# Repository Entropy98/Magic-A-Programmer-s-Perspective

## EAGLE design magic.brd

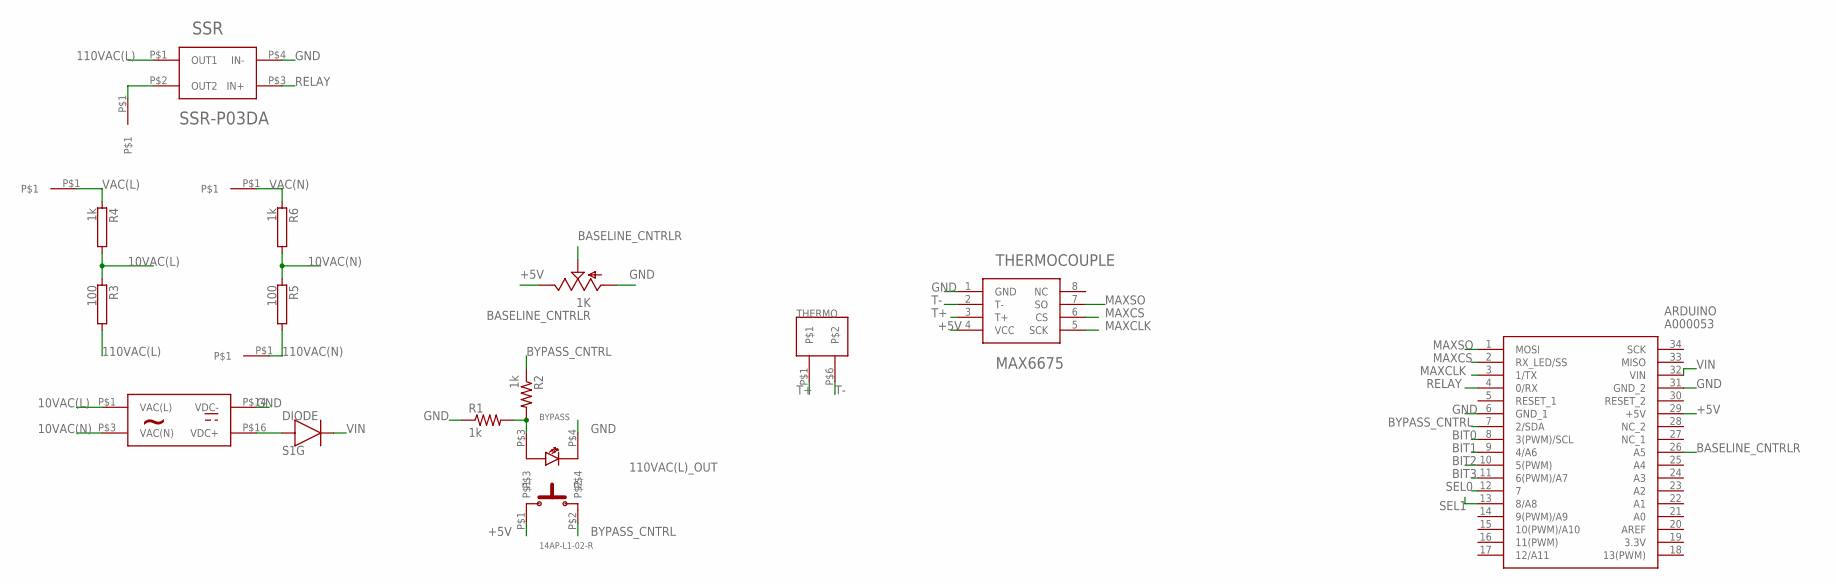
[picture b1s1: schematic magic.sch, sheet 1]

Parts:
110VAC(L)_OUT, 110VAC(N)_OUT: 6-GAUGE
AC(L)_IN: 6-GAUGE
AC(N)_IN: 6-GAUGE
ARDUINO: A000053; HDRV34W70P1570X254_2X17_4900X1
BASELINE_CNTRLR: 1K; PT-10
BYPASS: 14AP-L1-02-R; 14XX-LX-0X-X
DIODE: S1G
R1, R2: 1k; M1206
R3, R5: 100; TO-247-2V
R4, R6: 1k; TO-247-2V
SSR: SSR-P03DA
THERMO: PC6-16/2-G1-10,16
THERMOCOUPLE: MAX6675
TRANSFORMER: RAC04-09SC

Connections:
10VAC(L): R3.1, R4.2, TRANSFORMER.P$1 (VAC(L))
10VAC(N): R5.1, R6.2, TRANSFORMER.P$3 (VAC(N))
110VAC(L): R3.2, SSR.P$1 (OUT1)
110VAC(L)_OUT: 110VAC(L)_OUT.P$1, SSR.P$2 (OUT2)
110VAC(N): 110VAC(N)_OUT.P$1, R5.2
+5V: ARDUINO.29 (+5V), BASELINE_CNTRLR.E, BYPASS.P$1, THERMOCOUPLE.4 (VCC); also elsewhere on the board
BASELINE_CNTRLR: ARDUINO.26 (A5), BASELINE_CNTRLR.S
BIT0: ARDUINO.8 (3(PWM)/SCL); also elsewhere on the board
BIT1: ARDUINO.9 (4/A6); also elsewhere on the board
BIT2: ARDUINO.10 (5(PWM)); also elsewhere on the board
BIT3: ARDUINO.11 (6(PWM)/A7); also elsewhere on the board
BYPASS_CNTRL: ARDUINO.7 (2/SDA), BYPASS.P$2, R2.1
GND: ARDUINO.6 (GND_1), ARDUINO.31 (GND_2), BASELINE_CNTRLR.A, BYPASS.P$4, R1.1, SSR.P$4 (IN-), THERMOCOUPLE.1 (GND), TRANSFORMER.P$14 (VDC-); also elsewhere on the board
MAXCLK: ARDUINO.3 (1/TX), THERMOCOUPLE.5 (SCK)
MAXCS: ARDUINO.2 (RX_LED/SS), THERMOCOUPLE.6 (CS)
MAXSO: ARDUINO.1 (MOSI), THERMOCOUPLE.7 (SO)
unnamed: DIODE.2, TRANSFORMER.P$16 (VDC+)
unnamed: BYPASS.P$3, R1.2, R2.2
RELAY: ARDUINO.4 (0/RX), SSR.P$3 (IN+)
SEL0: ARDUINO.12 (7); also elsewhere on the board
SEL1: ARDUINO.13 (8/A8); also elsewhere on the board
T+: THERMO.P$1, THERMOCOUPLE.3 (T+)
T-: THERMO.P$6, THERMOCOUPLE.2 (T-)
VAC(L): AC(L)_IN.P$1, R4.1
VAC(N): AC(N)_IN.P$1, R6.1
VIN: ARDUINO.32 (VIN), DIODE.1

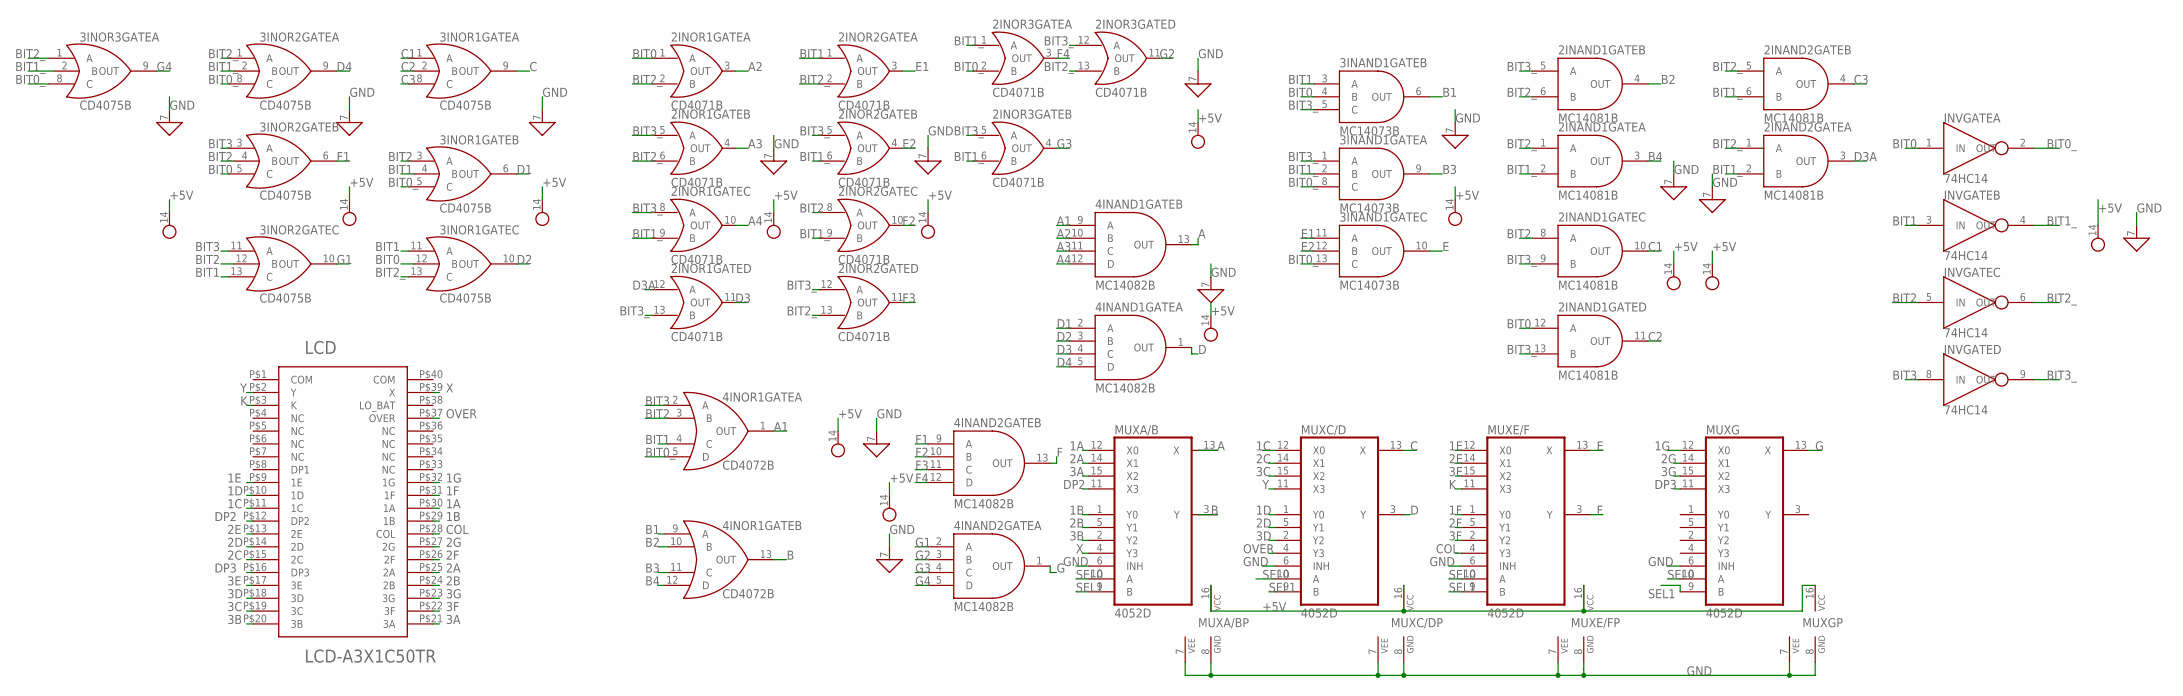
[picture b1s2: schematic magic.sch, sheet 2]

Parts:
2INAND1, 2INAND2: MC14081B; MC140XXBG
2INOR1, 2INOR2, 2INOR3: CD4071B; CD407XB
3INAND1: MC14073B; MC140XXBG
3INOR1, 3INOR2, 3INOR3: CD4075B; CD407XB
4INAND1, 4INAND2: MC14082B; MC140XXBG
4INOR1: CD4072B; CD407XB
INV: 74HC14
LCD: LCD-A3X1C50TR
MUXA/B: 4052D; SO16
MUXC/D: 4052D; SO16
MUXE/F: 4052D; SO16
MUXG: 4052D; SO16

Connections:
1A: LCD.P$30 (1A), MUXA/B.12 (X0)
1B: LCD.P$29 (1B), MUXA/B.1 (Y0)
1C: LCD.P$11 (1C), MUXC/D.12 (X0)
1D: LCD.P$10 (1D), MUXC/D.1 (Y0)
1E: LCD.P$9 (1E), MUXE/F.12 (X0)
1F: LCD.P$31 (1F), MUXE/F.1 (Y0)
1G: LCD.P$32 (1G), MUXG.12 (X0)
2A: LCD.P$25 (2A), MUXA/B.14 (X1)
2B: LCD.P$24 (2B), MUXA/B.5 (Y1)
2C: LCD.P$15 (2C), MUXC/D.14 (X1)
2D: LCD.P$14 (2D), MUXC/D.5 (Y1)
2E: LCD.P$13 (2E), MUXE/F.14 (X1)
2F: LCD.P$26 (2F), MUXE/F.5 (Y1)
2G: LCD.P$27 (2G), MUXG.14 (X1)
3A: LCD.P$21 (3A), MUXA/B.15 (X2)
3B: LCD.P$20 (3B), MUXA/B.2 (Y2)
3C: LCD.P$19 (3C), MUXC/D.15 (X2)
3D: LCD.P$18 (3D), MUXC/D.2 (Y2)
3E: LCD.P$17 (3E), MUXE/F.15 (X2)
3F: LCD.P$22 (3F), MUXE/F.2 (Y2)
3G: LCD.P$23 (3G), MUXG.15 (X2)
+5V: 2INAND1.14 (1), 2INAND2.14 (1), 2INOR1.14 (1), 2INOR2.14 (1), 2INOR3.14 (1), 3INAND1.14 (1), 3INOR1.14 (1), 3INOR2.14 (1), 3INOR3.14 (1), 4INAND1.14 (1), 4INAND2.14 (1), 4INOR1.14 (1), INV.14 (1), MUXA/B.16 (VCC), MUXC/D.16 (VCC), MUXE/F.16 (VCC), MUXG.16 (VCC); also elsewhere on the board
A: 4INAND1.13 (OUT), MUXA/B.13 (X)
A1: 4INAND1.9 (A), 4INOR1.1 (OUT)
A2: 2INOR1.3 (OUT), 4INAND1.10 (B)
A3: 2INOR1.4 (OUT), 4INAND1.11 (C)
A4: 2INOR1.10 (OUT), 4INAND1.12 (D)
B: 4INOR1.13 (OUT), MUXA/B.3 (Y)
B1: 3INAND1.6 (OUT), 4INOR1.9 (A)
B2: 2INAND1.4 (OUT), 4INOR1.10 (B)
B3: 3INAND1.9 (OUT), 4INOR1.11 (C)
B4: 2INAND1.3 (OUT), 4INOR1.12 (D)
BIT0: 2INAND1.12 (A), 2INOR1.1 (A), 3INAND1.4 (B), 3INOR1.12 (B), 3INOR2.5 (C), INV.1 (IN); also elsewhere on the board
BIT0_: 2INOR3.2 (B), 3INAND1.8 (C), 3INAND1.13 (C), 3INOR1.5 (C), 3INOR2.8 (C), 3INOR3.8 (C), 4INOR1.5 (D), INV.2 (OUT)
BIT1: 2INOR2.1 (A), 3INAND1.3 (A), 3INOR1.4 (B), 3INOR1.11 (A), 3INOR2.13 (C), 4INOR1.4 (C), INV.3 (IN); also elsewhere on the board
BIT1_: 2INAND1.2 (B), 2INAND2.2 (B), 2INAND2.6 (B), 2INOR1.9 (B), 2INOR2.6 (B), 2INOR2.9 (B), 2INOR3.1 (A), 2INOR3.6 (B), 3INAND1.2 (B), 3INOR2.2 (B), 3INOR3.2 (B), INV.4 (OUT)
BIT2: 2INAND1.8 (A), 2INOR2.8 (A), 3INOR1.3 (A), 3INOR2.4 (B), 3INOR2.12 (B), 4INOR1.3 (B), INV.5 (IN); also elsewhere on the board
BIT2_: 2INAND1.1 (A), 2INAND1.6 (B), 2INAND2.1 (A), 2INAND2.5 (A), 2INOR1.2 (B), 2INOR1.6 (B), 2INOR2.2 (B), 2INOR2.13 (B), 2INOR3.13 (B), 3INOR1.13 (C), 3INOR2.1 (A), 3INOR3.1 (A), INV.6 (OUT)
BIT3: 3INOR2.3 (A), 3INOR2.11 (A), 4INOR1.2 (A), INV.8 (IN); also elsewhere on the board
BIT3_: 2INAND1.5 (A), 2INAND1.9 (B), 2INAND1.13 (B), 2INOR1.5 (A), 2INOR1.8 (A), 2INOR1.13 (B), 2INOR2.5 (A), 2INOR2.12 (A), 2INOR3.5 (A), 2INOR3.12 (A), 3INAND1.1 (A), 3INAND1.5 (C), INV.9 (OUT)
C: 3INOR1.9 (OUT), MUXC/D.13 (X)
C1: 2INAND1.10 (OUT), 3INOR1.1 (A)
C2: 2INAND1.11 (OUT), 3INOR1.2 (B)
C3: 2INAND2.4 (OUT), 3INOR1.8 (C)
COL: LCD.P$28 (COL), MUXE/F.4 (Y3)
D: 4INAND1.1 (OUT), MUXC/D.3 (Y)
D1: 3INOR1.6 (OUT), 4INAND1.2 (A)
D2: 3INOR1.10 (OUT), 4INAND1.3 (B)
D3: 2INOR1.11 (OUT), 4INAND1.4 (C)
D3A: 2INAND2.3 (OUT), 2INOR1.12 (A)
D4: 3INOR2.9 (OUT), 4INAND1.5 (D)
DP2: LCD.P$12 (DP2), MUXA/B.11 (X3)
DP3: LCD.P$16 (DP3), MUXG.11 (X3)
E: 3INAND1.10 (OUT), MUXE/F.13 (X)
E1: 2INOR2.3 (OUT), 3INAND1.11 (A)
E2: 2INOR2.4 (OUT), 3INAND1.12 (B)
F: 4INAND2.13 (OUT), MUXE/F.3 (Y)
F1: 3INOR2.6 (OUT), 4INAND2.9 (A)
F2: 2INOR2.10 (OUT), 4INAND2.10 (B)
F3: 2INOR2.11 (OUT), 4INAND2.11 (C)
F4: 2INOR3.3 (OUT), 4INAND2.12 (D)
G: 4INAND2.1 (OUT), MUXG.13 (X)
G1: 3INOR2.10 (OUT), 4INAND2.2 (A)
G2: 2INOR3.11 (OUT), 4INAND2.3 (B)
G3: 2INOR3.4 (OUT), 4INAND2.4 (C)
G4: 3INOR3.9 (OUT), 4INAND2.5 (D)
GND: 2INAND1.7 (1), 2INAND2.7 (1), 2INOR1.7 (1), 2INOR2.7 (1), 2INOR3.7 (1), 3INAND1.7 (1), 3INOR1.7 (1), 3INOR2.7 (1), 3INOR3.7 (1), 4INAND1.7 (1), 4INAND2.7 (1), 4INOR1.7 (1), INV.7 (1), MUXA/B.6 (INH), MUXA/B.7 (VEE), MUXA/B.8 (GND), MUXC/D.6 (INH), MUXC/D.7 (VEE), MUXC/D.8 (GND), MUXE/F.6 (INH), MUXE/F.7 (VEE), MUXE/F.8 (GND), MUXG.6 (INH), MUXG.7 (VEE), MUXG.8 (GND); also elsewhere on the board
K: LCD.P$3 (K), MUXE/F.11 (X3)
OVER: LCD.P$37 (OVER), MUXC/D.4 (Y3)
SEL0: MUXA/B.10 (A), MUXC/D.10 (A), MUXE/F.10 (A), MUXG.10 (A); also elsewhere on the board
SEL1: MUXA/B.9 (B), MUXC/D.9 (B), MUXE/F.9 (B), MUXG.9 (B); also elsewhere on the board
X: LCD.P$39 (X), MUXA/B.4 (Y3)
Y: LCD.P$2 (Y), MUXC/D.11 (X3)

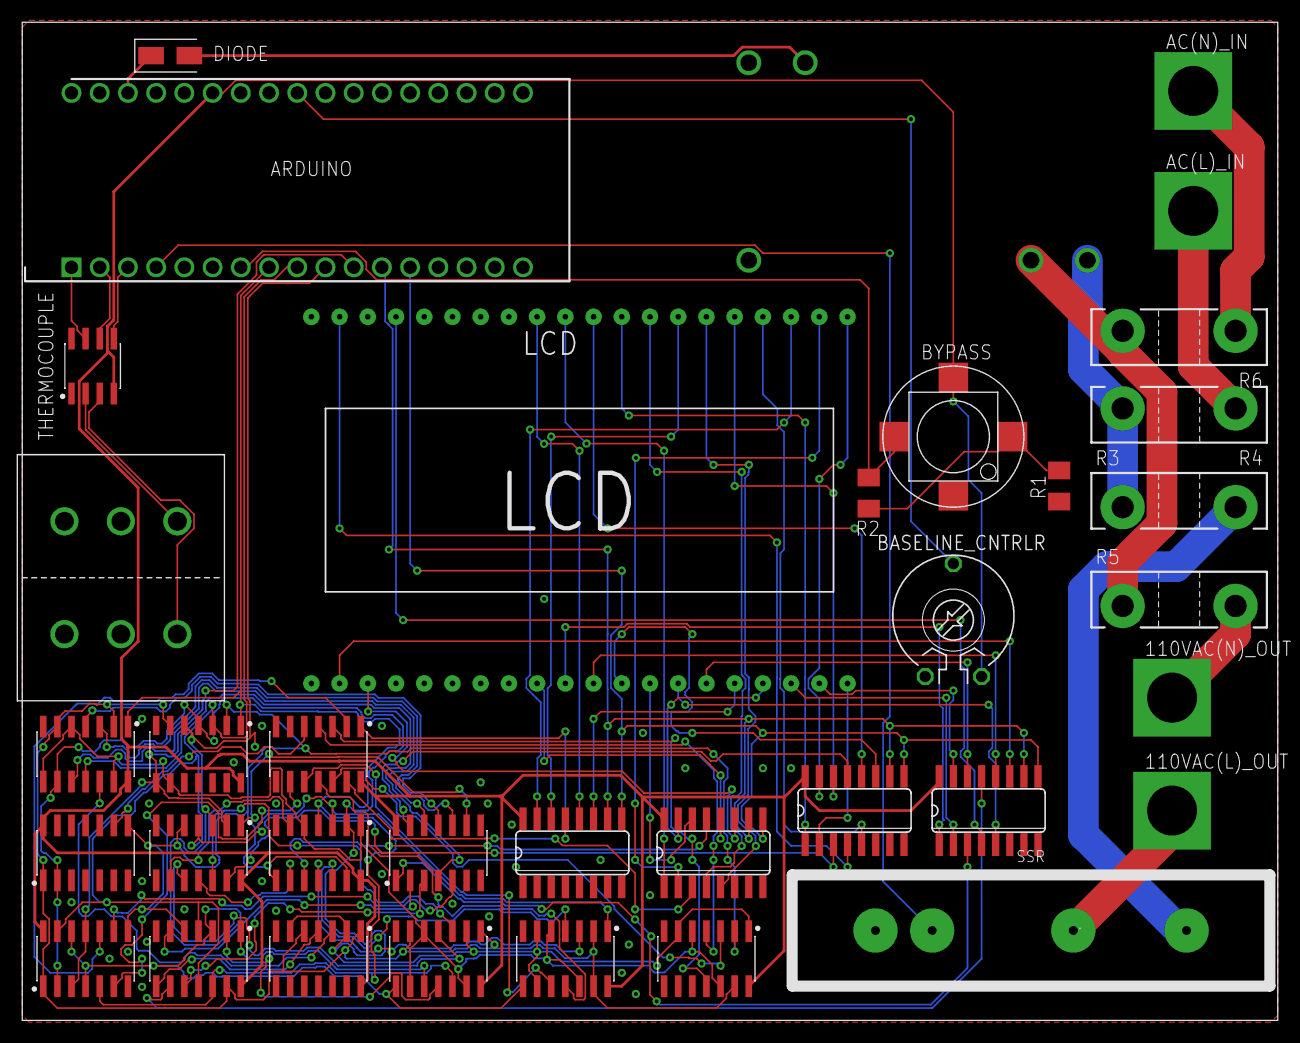
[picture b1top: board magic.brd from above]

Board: 2 copper layers, 113.0 x 89.8 mm, 36 parts (1 on the bottom side), 91 nets.

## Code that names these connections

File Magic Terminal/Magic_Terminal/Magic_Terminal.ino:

#include <max6675.h>
#include <SPI.h>
#include <Adafruit_ST7735.h>
#include <Adafruit_GFX.h>

#define sclk 13
#define mosi 11
#define cs   10
#define dc   9
#define rst  8

#define baselineController 5
#define bypassControl 5
#define relay 4

#define maxSO 1
#define maxCS 2
#define maxCLK 3

MAX6675 ktc(maxCLK, maxCS, maxSO);

#define FRINGE_BLUE 0x001F
#define FRINGE_YELLOW 0xFFE0

#define tempUpBound 210
#define tempLowBound 0

Adafruit_ST7735 tft = Adafruit_ST7735(cs, dc, mosi, sclk, rst);

int baselineTemp=667;
bool alwaysOnBypass=false;
int atmosphericTemp=0;
int IRread1=0;
int IRread2=0;
int IRread3=0;
bool relayState=false;

int buttonState=0;

void setup() {
  Serial.begin(9600);
  tft.initR(INITR_BLACKTAB);   // initialize a ST7735S chip, black tab

  pinMode(bypassControl, OUTPUT); //turns off temp regulation
  pinMode(relay,OUTPUT); //controls flow of AC current to wheel heater
  
  uint16_t time = millis();
  time = millis() - time;

  delay(500);

  tft.fillScreen(FRINGE_BLUE);
  drawText(30,10,2,"Fringe",FRINGE_YELLOW);
  drawText(20,30,1,"Magic: Terminal",FRINGE_YELLOW);
  delay(1000);

}

void drawText(int x, int y,int weight,char *text, uint16_t color) {
  tft.setCursor(x, y);
  tft.setTextColor(color);
  tft.setTextWrap(true);
  tft.setTextSize(weight);
  tft.print(text);
}

void loop() {
  //values for comparison
  int oldBaseline=baselineTemp;
  bool oldAlwaysOnBypass=alwaysOnBypass;
  int oldAtmospheric=atmosphericTemp;
  bool oldRelayState=relayState;

  atmosphericTemp=ktc.readFahrenheit();//temp sensor read in

  //binary On/Off control of relay
  if(atmosphericTemp<baselineTemp){
    digitalWrite(relay,HIGH);
    relayState=true;
  }
  else{
    digitalWrite(relay,LOW);
    relayState=false;
  }
  

  //float R = 1023.0/((float)atmosphericTemp)-1.0;
  //R = 100000.0*R;
  //convert to temperature via datasheet ;
  //float temperature=((1.0/(log(R/100000.0)/4275+1/298.15)-273.15)*9/5)+32;

  //Serial.println(temperature);
  //atmosphericTemp=int(temperature);

  
  int baselineControl=analogRead(baselineController); //adjustable baseline based on potentiometer input
  Serial.println(baselineControl);
  float baselineTempRatio=baselineControl/1023.0; //convert pot value to percentage
  baselineTemp=int(baselineTempRatio*210); //create baseline temp based on desired max temp of 210F and return to type int

  buttonState=digitalRead(bypassControl); //bypass controller
  if(buttonState==HIGH){
    alwaysOnBypass=!alwaysOnBypass;
    delay(200);
  }

  //baseline refresh
  if(baselineTemp!=oldBaseline){
    tft.fillRect(5,50,tft.width(),10,FRINGE_BLUE);
  }
  //bypass refresh
  if(alwaysOnBypass!=oldAlwaysOnBypass){
    tft.fillRect(5,60,tft.width(),10,FRINGE_BLUE);
  }

  //atmospheric refresh
  if(oldAtmospheric!=atmosphericTemp){
    tft.fillRect(5,70,tft.width(),10,FRINGE_BLUE);
  }

  //power refreshes
  if(oldRelayState!=relayState){
    tft.fillRect(5,80,tft.width(),10,FRINGE_BLUE);
  }

  drawText(30,10,2,"Fringe",FRINGE_YELLOW);
  drawText(20,30,1,"Magic: Terminal",FRINGE_YELLOW);

  //baseline display
  tft.setCursor(5,50);
  tft.setTextColor(FRINGE_YELLOW);
  tft.setTextSize(0);
  tft.print("Baseline Temp:");
  tft.print(baselineTemp);
  tft.print("F");

  //bypass display
  tft.setCursor(5,60);
  tft.setTextColor(FRINGE_YELLOW);
  tft.setTextSize(0);
  tft.print("Always On Bypass:");
  if(alwaysOnBypass){
    tft.print("On");
  }
  else{
    tft.print("Off");
  }

  //atmospheric temp display
  tft.setCursor(5,70);
  tft.setTextColor(FRINGE_YELLOW);
  tft.setTextSize(0);
  tft.print("Atmosphere Temp:");
  tft.print(atmosphericTemp);
  tft.print("F");

  //power read display
  tft.setCursor(5,80);
  tft.setTextColor(FRINGE_YELLOW);
  tft.setTextSize(0);
  tft.print("Power ");
  if(relayState){
    tft.print("On");
  }
  else{
    tft.print("Off");
  }

}

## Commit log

2019-03-26 Initial Overleaf Import
2020-01-22 board files
2020-01-25 ino files
2020-01-28 magic eagle library
2020-02-04 thermocouple block
2020-02-05 transformer
2020-02-06 redid the board
2020-02-06 widened AC traces for 1oz copper and made gerber files
